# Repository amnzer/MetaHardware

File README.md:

# MetaHardware
Hardware for MetaSense's KiCad design. 

hardware_v1 is the PCB version used for the prototype mentioned in the final report. 

hardware_v2 aims to fix a few of the major problems that hardware_v1 has in terms of reliability and simplicity, although we have not yet tested hardware_v2. hardware_v2 is the more natural starting point for the next team to pick up the MetaSense project

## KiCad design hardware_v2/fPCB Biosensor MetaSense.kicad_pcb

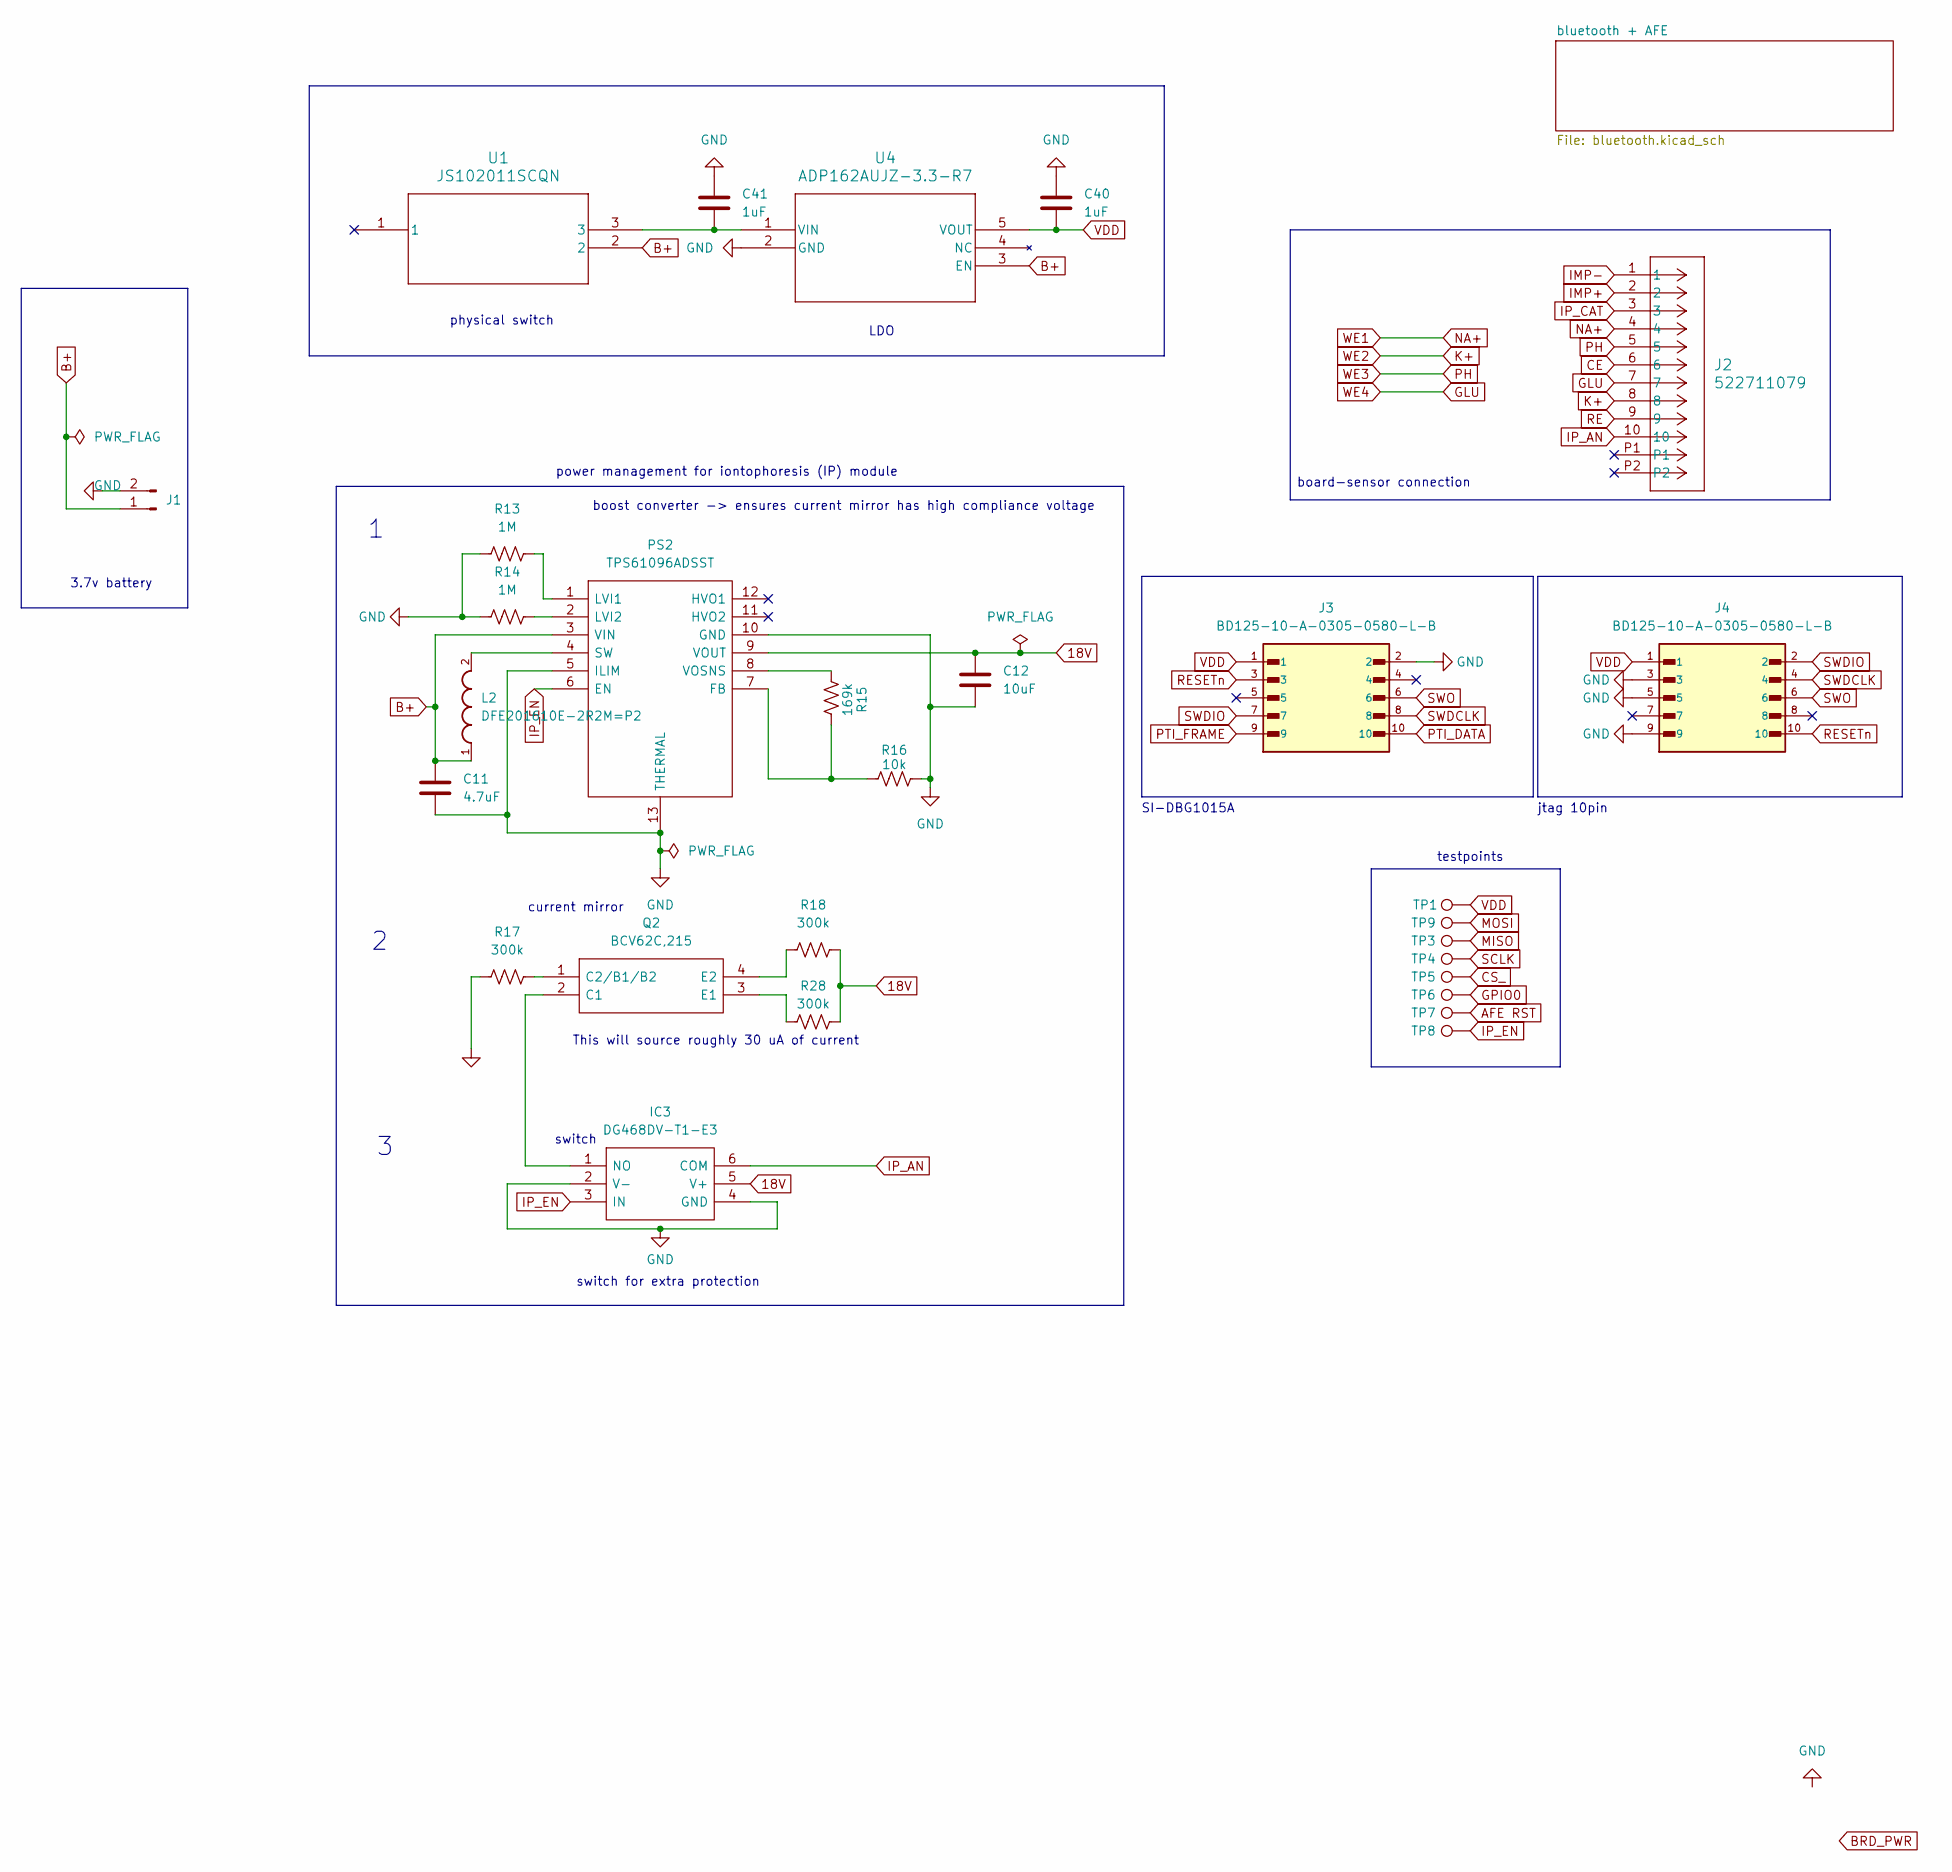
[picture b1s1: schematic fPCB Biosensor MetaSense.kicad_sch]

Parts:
C11: 4.7uF; C_0603_1608Metric
C12: 10uF; C_1206_3216Metric
C40, C41: 1uF; C_0603_1608Metric
IC3: DG468DV-T1-E3; TSOP6_DG_VIS; Mouser Part Number 781-DG468DV-E3
J1: Conn_01x02_Pin; PinHeader_1x02_P2.54mm_Vertical
J2: 522711079; CON_522711079_MOL
J3, J4: BD125-10-A-0305-0580-L-B; CONN_BD125-10-x-0305-0580-L-x_GCT; PARTREV A
L2: DFE201610E-2R2M=P2
PS2: TPS61096ADSST; DSS0012A; Mouser Part Number 595-TPS61096ADSST
Q2: BCV62C,215; BCV62C215; Mouser Part Number 771-BCV62C-T/R
R13, R14: 1M; R_0603_1608Metric_Pad0.98x0.95mm_HandSolder
R15: 169k; R_0603_1608Metric_Pad0.98x0.95mm_HandSolder
R16: 10k; R_0603_1608Metric_Pad0.98x0.95mm_HandSolder
R17, R18, R28: 300k; R_0603_1608Metric_Pad0.98x0.95mm_HandSolder
TP1, TP3, TP4, TP5, TP6, TP7, TP8, TP9: TestPoint; TestPoint_THTPad_1.5x1.5mm_Drill0.7mm
U1: JS102011SCQN; SWITCH_1SCQN
U4: ADP162AUJZ-3.3-R7

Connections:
18V: C12.1, IC3.5 (V+), PS2.9 (VOUT), R18.2, R28.2; also elsewhere on the board
AFE RST: TP7.1; also elsewhere on the board
B+: C11.1, J1.1, L2.1, PS2.3 (VIN), U1.2, U4.3 (EN); also elsewhere on the board
CE: J2.6; also elsewhere on the board
CS_: TP5.1; also elsewhere on the board
GLU: J2.7; also elsewhere on the board
GND: C11.2, C12.2, C40.2, C41.2, IC3.2 (V-), IC3.4 (GND), J1.2, J3.2, J4.3, J4.5, J4.9, PS2.5 (ILIM), PS2.10 (GND), PS2.13 (THERMAL), PS2.V, R13.1, R14.1, R16.1, R17.1, U4.2 (GND); also elsewhere on the board
IMP+: J2.2; also elsewhere on the board
IMP-: J2.1; also elsewhere on the board
IP_AN: IC3.6 (COM), J2.10
IP_CAT: J2.3; also elsewhere on the board
IP_EN: IC3.3 (IN), PS2.6 (EN), TP8.1; also elsewhere on the board
K+: J2.8; also elsewhere on the board
MISO: TP3.1; also elsewhere on the board
MOSI: TP9.1; also elsewhere on the board
NA+: J2.4; also elsewhere on the board
unnamed: IC3.1 (NO), Q2.2 (C1)
unnamed: PS2.7 (FB), R15.1, R16.2
unnamed: PS2.1 (LVI1), R13.2
unnamed: PS2.2 (LVI2), R14.2
unnamed: L2.2, PS2.4 (SW)
unnamed: PS2.8 (VOSNS), R15.2
unnamed: Q2.1 (C2/B1/B2), R17.2
unnamed: Q2.3 (E1), R28.1
unnamed: Q2.4 (E2), R18.1
unnamed: C41.1, U1.3, U4.1 (VIN)
PH: J2.5; also elsewhere on the board
PTI_DATA: J3.10; also elsewhere on the board
PTI_FRAME: J3.9; also elsewhere on the board
RE: J2.9; also elsewhere on the board
RESETn: J3.3, J4.10; also elsewhere on the board
SCLK: TP4.1; also elsewhere on the board
SWDCLK: J3.8, J4.4; also elsewhere on the board
SWDIO: J3.7, J4.2; also elsewhere on the board
SWO: J3.6, J4.6; also elsewhere on the board
VDD: C40.1, J3.1, J4.1, TP1.1, U4.5 (VOUT); also elsewhere on the board

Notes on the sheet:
current mirror
power management for iontophoresis (IP) module
LDO
boost converter -> ensures current mirror has high compliance voltage
This will source roughly 30 uA of current
switch
board-sensor connection
switch for extra protection
SI-DBG1015A
jtag 10pin
3.7v battery
physical switch
testpoints

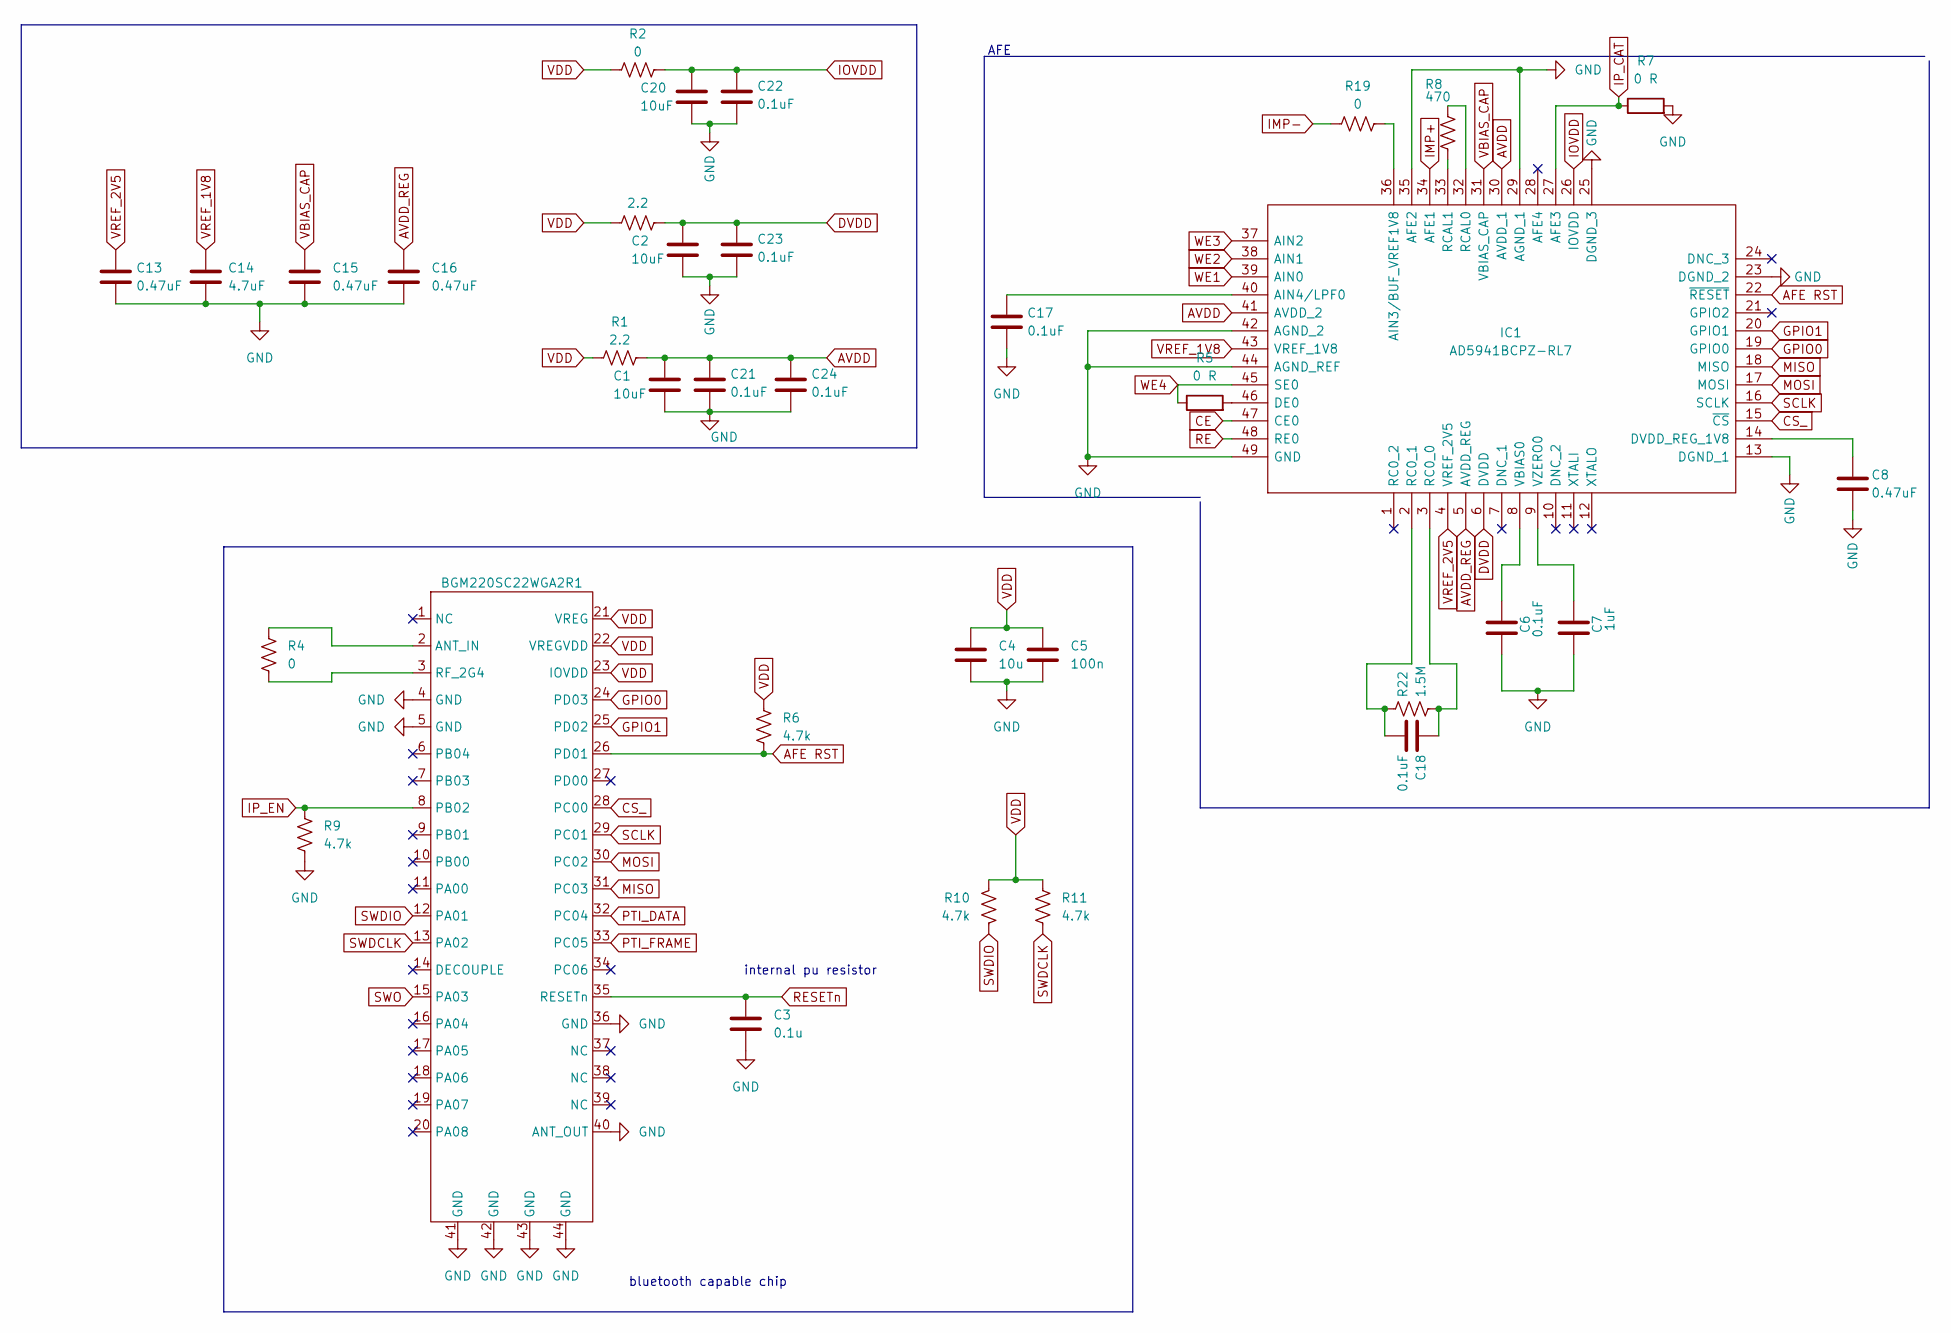
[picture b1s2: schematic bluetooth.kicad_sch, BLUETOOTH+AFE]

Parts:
BGM220SC22WGA2R1: BGM220SC22WGA2R
C1, C2, C20: 10uF; C_1206_3216Metric
C3: 0.1u; C_0603_1608Metric
C4: 10u; C_0603_1608Metric_Pad1.08x0.95mm_HandSolder
C5: 100n; C_0603_1608Metric_Pad1.08x0.95mm_HandSolder
C6, C17, C18, C21, C22, C23, C24: 0.1uF; C_0603_1608Metric
C7: 1uF; C_0603_1608Metric
C8, C13, C15, C16: 0.47uF; C_0603_1608Metric
C14: 4.7uF; C_0603_1608Metric
IC1: AD5941BCPZ-RL7; QFN50P700X700X80-49N; Mouser Part Number 584-AD5941BCPZ-RL7
R1, R3: 2.2; R_0603_1608Metric_Pad0.98x0.95mm_HandSolder
R2, R19: 0; R_0603_1608Metric_Pad0.98x0.95mm_HandSolder
R4: 0; RES_ERJ1G_PAN
R5, R7: 0 R; R_0603_1608Metric_Pad0.98x0.95mm_HandSolder
R6, R9, R10, R11: 4.7k; R_0603_1608Metric
R8: 470; R_0603_1608Metric_Pad0.98x0.95mm_HandSolder
R22: 1.5M; R_0603_1608Metric_Pad0.98x0.95mm_HandSolder

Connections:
AFE RST: BGM220SC22WGA2R1.26 (PD01), IC1.22 (~RESET), R6.2; also elsewhere on the board
AVDD: C1.1, C21.1, C24.1, IC1.30 (AVDD_1), IC1.41 (AVDD_2), R1.2
AVDD_REG: C16.1, IC1.5 (AVDD_REG)
CE: IC1.47 (CE0); also elsewhere on the board
CS_: BGM220SC22WGA2R1.28 (PC00), IC1.15 (~CS); also elsewhere on the board
DVDD: C2.1, C23.1, IC1.6 (DVDD), R3.2
GLU: IC1.45 (SE0), R5.1; also elsewhere on the board
GND: BGM220SC22WGA2R1.4 (GND), BGM220SC22WGA2R1.5 (GND), BGM220SC22WGA2R1.36 (GND), BGM220SC22WGA2R1.40 (ANT_OUT), BGM220SC22WGA2R1.41 (GND), BGM220SC22WGA2R1.42 (GND), BGM220SC22WGA2R1.43 (GND), BGM220SC22WGA2R1.44 (GND), C1.2, C2.2, C3.2, C4.2, C5.2, C6.1, C7.1, C8.2, C13.2, C14.2, C15.2, C16.2, C17.2, C20.2, C21.2, C22.2, C23.2, C24.2, IC1.13 (DGND_1), IC1.23 (DGND_2), IC1.25 (DGND_3), IC1.29 (AGND_1), IC1.35 (AFE2), IC1.42 (AGND_2), IC1.44 (AGND_REF), IC1.49 (GND), R7.2, R9.2; also elsewhere on the board
GPIO0: BGM220SC22WGA2R1.24 (PD03), IC1.19 (GPIO0)
GPIO1: BGM220SC22WGA2R1.25 (PD02), IC1.20 (GPIO1)
IMP+: IC1.34 (AFE1); also elsewhere on the board
IMP-: R19.1; also elsewhere on the board
IOVDD: C20.1, C22.1, IC1.26 (IOVDD), R2.2
IP_CAT: IC1.27 (AFE3), R7.1; also elsewhere on the board
IP_EN: BGM220SC22WGA2R1.8 (PB02), R9.1; also elsewhere on the board
K+: IC1.38 (AIN1); also elsewhere on the board
MISO: BGM220SC22WGA2R1.31 (PC03), IC1.18 (MISO); also elsewhere on the board
MOSI: BGM220SC22WGA2R1.30 (PC02), IC1.17 (MOSI); also elsewhere on the board
NA+: IC1.39 (AIN0); also elsewhere on the board
unnamed: BGM220SC22WGA2R1.2 (ANT_IN), R4.1
unnamed: BGM220SC22WGA2R1.3 (RF_2G4), R4.2
unnamed: IC1.36 (AIN3/BUF_VREF1V8), R19.2
unnamed: C17.1, IC1.40 (AIN4/LPF0)
unnamed: IC1.46 (DE0), R5.2
unnamed: C8.1, IC1.14 (DVDD_REG_1V8)
unnamed: C18.1, IC1.3 (RC0_0), R22.2
unnamed: C18.2, IC1.2 (RC0_1), R22.1
unnamed: IC1.32 (RCAL0), R8.1
unnamed: IC1.33 (RCAL1), R8.2
unnamed: C6.2, IC1.8 (VBIAS0)
unnamed: C7.2, IC1.9 (VZERO0)
PH: IC1.37 (AIN2); also elsewhere on the board
PTI_DATA: BGM220SC22WGA2R1.32 (PC04); also elsewhere on the board
PTI_FRAME: BGM220SC22WGA2R1.33 (PC05); also elsewhere on the board
RE: IC1.48 (RE0); also elsewhere on the board
RESETn: BGM220SC22WGA2R1.35 (RESETn), C3.1; also elsewhere on the board
SCLK: BGM220SC22WGA2R1.29 (PC01), IC1.16 (SCLK); also elsewhere on the board
SWDCLK: BGM220SC22WGA2R1.13 (PA02), R11.2; also elsewhere on the board
SWDIO: BGM220SC22WGA2R1.12 (PA01), R10.2; also elsewhere on the board
SWO: BGM220SC22WGA2R1.15 (PA03); also elsewhere on the board
VBIAS_CAP: C15.1, IC1.31 (VBIAS_CAP)
VDD: BGM220SC22WGA2R1.21 (VREG), BGM220SC22WGA2R1.22 (VREGVDD), BGM220SC22WGA2R1.23 (IOVDD), C4.1, C5.1, R1.1, R2.1, R3.1, R6.1, R10.1, R11.1; also elsewhere on the board
VREF_1V8: C14.1, IC1.43 (VREF_1V8)
VREF_2V5: C13.1, IC1.4 (VREF_2V5)

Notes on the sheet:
AFE
internal pu resistor
bluetooth capable chip

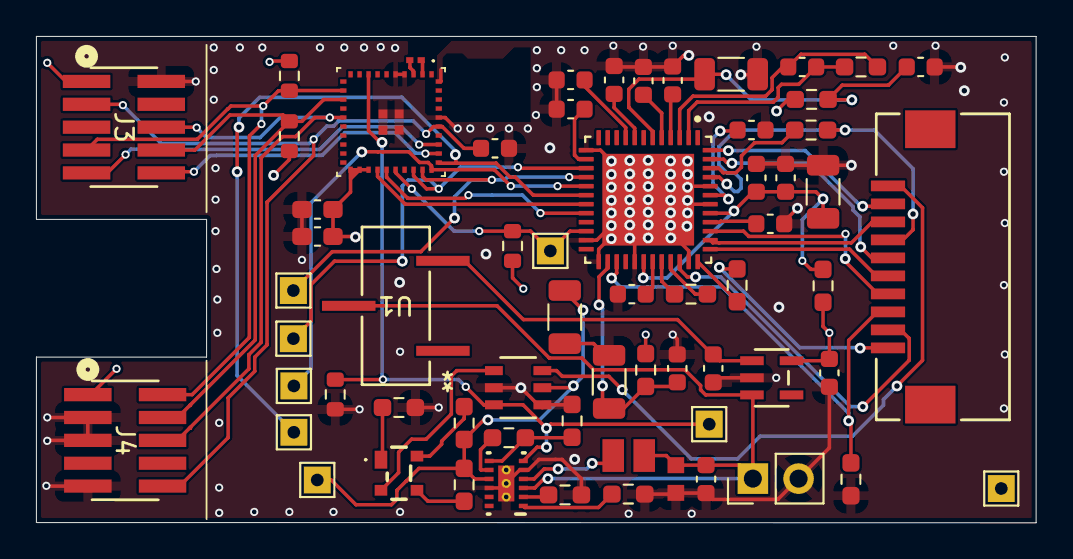
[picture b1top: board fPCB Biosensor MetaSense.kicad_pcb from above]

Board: 4 copper layers, 55.5 x 27.0 mm, 64 parts (0 on the bottom side), 57 nets.

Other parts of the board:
C37: GRM188R60J106ME47D
TP10: TestPoint; TestPoint_THTPad_1.5x1.5mm_Drill0.7mm

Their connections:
18V: TP10.1; also elsewhere on the board
B+: C37.2; also elsewhere on the board
GND: C37.1; also elsewhere on the board

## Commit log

2026-05-03 Update README with hardware version information
    Added details about hardware_v1 and hardware_v2 versions.
2026-05-07 add hardware
